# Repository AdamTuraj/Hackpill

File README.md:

# 

**The Hackboard may be overkill, but Hackpill is here to fill the smaller shoes!**

The Hackpill is a small but versatile board at a small cost.

Hackpill has the following features:

- 48MHz Cortex M0 Core with 32 Kb of Flash and 6 Kb of SRAM
- 32 GPIO pins
  - 1 SPI Interfaces
  - 1 I2C Interface
  - 1 CAN Interface
  - 1 USART Interface
  - 1 I2S Interface
  - 11 PWM Pins
  - 10 ADC's (Analog pins)
- An addressable LED
- USB C port for flashing and power

## Assembly

> [!CAUTION]
> The USBLC6 and diode may be orientated wrong. Ensure all components are properly orientated before ordering!

This board can be assembled through JLCPCB. The price for 5 assembled boards is around $35 USD without headers.

### Work with Arduino

> [!NOTE]
> You must have an STLink to continue. They can be bought standalone or with a Nucleo board.

A more detailed guide will be written up shortly. You may now use [STM32Duino](https://github.com/stm32duino/Arduino_Core_STM32) to make it work with Arduino.

## License

Hackclub is licensed under the MIT License. See the full license text in [LICENSE](LICENSE).

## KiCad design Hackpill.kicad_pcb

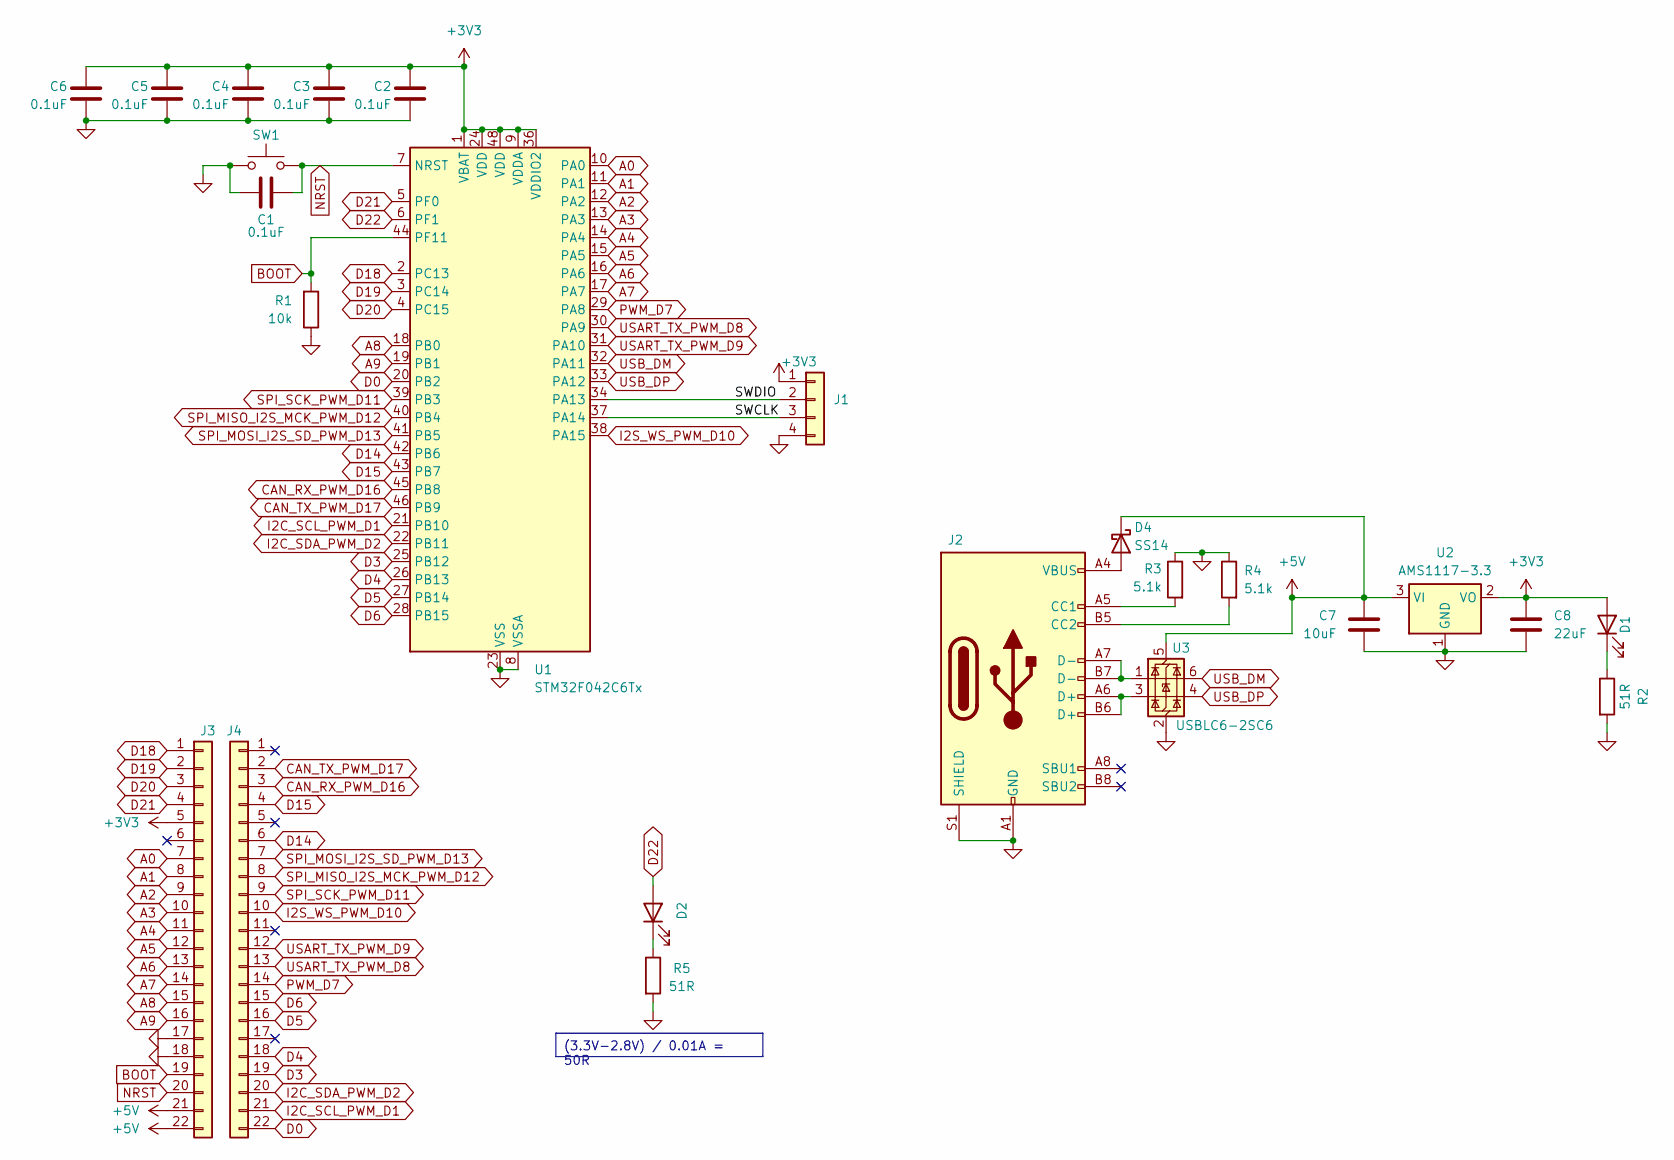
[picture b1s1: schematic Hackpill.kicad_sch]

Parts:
C1, C2, C3, C4, C5, C6: 0.1uF; C_0603_1608Metric
C7: 10uF; C_0603_1608Metric
C8: 22uF; C_0603_1608Metric
D1, D2: LED; LED_0805_2012Metric; LCSC C2297
D4: SS14; D_SMA
J1: Conn_01x04; PinHeader_1x04_P2.54mm_Vertical; LCSC C18905864
J2: USB_C_Receptacle_USB2.0_16P; USB_C_Receptacle_Shouhan_16P_TopMnt_Horizontal; LCSC C6332269
J3: Conn_01x22; PinSocket_1x22_P2.54mm_Vertical
J4: Conn_01x22; PinSocket_1x22_P2.54mm_Vertical; LCSC C18078140
R1: 10k; R_0603_1608Metric
R2, R5: 51R; R_0603_1608Metric
R3, R4: 5.1k; R_0603_1608Metric
SW1: SW_Push; SW_Push_1P1T_XKB_TS-1187A; LCSC C318884
U1: STM32F042C6Tx; LQFP-48_7x7mm_P0.5mm; LCSC C88447
U2: AMS1117-3.3; SOT-223-3_TabPin2; LCSC C6186
U3: USBLC6-2SC6; SOT-23-6; LCSC C2827654

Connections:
+3V3: C2.1, C3.1, C4.1, C5.1, C6.1, C8.1, D1.2 (A), J1.1, J3.5, U1.1 (VBAT), U1.9 (VDDA), U1.24 (VDD), U1.36 (VDDIO2), U1.48 (VDD), U2.2 (VO)
+5V: C7.1, D4.1 (K), J3.21, J3.22, U2.3 (VI), U3.5 (VBUS)
/SWCLK: J1.3, U1.37 (PA14)
/SWDIO: J1.2, U1.34 (PA13)
A0: J3.7, U1.10 (PA0)
A1: J3.8, U1.11 (PA1)
A2: J3.9, U1.12 (PA2)
A3: J3.10, U1.13 (PA3)
A4: J3.11, U1.14 (PA4)
A5: J3.12, U1.15 (PA5)
A6: J3.13, U1.16 (PA6)
A7: J3.14, U1.17 (PA7)
A8: J3.15, U1.18 (PB0)
A9: J3.16, U1.19 (PB1)
BOOT: J3.19, R1.2, U1.44 (PF11)
CAN_RX_PWM_D16: J4.3, U1.45 (PB8)
CAN_TX_PWM_D17: J4.2, U1.46 (PB9)
D0: J4.22, U1.20 (PB2)
D3: J4.19, U1.25 (PB12)
D4: J4.18, U1.26 (PB13)
D5: J4.16, U1.27 (PB14)
D6: J4.15, U1.28 (PB15)
D14: J4.6, U1.42 (PB6)
D15: J4.4, U1.43 (PB7)
D18: J3.1, U1.2 (PC13)
D19: J3.2, U1.3 (PC14)
D20: J3.3, U1.4 (PC15)
D21: J3.4, U1.5 (PF0)
D22: D2.2 (A), U1.6 (PF1)
GND: C1.1, C2.2, C3.2, C4.2, C5.2, C6.2, C7.2, C8.2, J1.4, J2.A1 (GND), J2.A12 (GND), J2.B1 (GND), J2.B12 (GND), J2.S1 (SHIELD), J3.17, J3.18, R1.1, R2.2, R3.1, R4.1, R5.2, SW1.1, U1.8 (VSSA), U1.23 (VSS), U1.35 (VSS), U1.47 (VSS), U2.1 (GND), U3.2 (GND)
I2C_SCL_PWM_D1: J4.21, U1.21 (PB10)
I2C_SDA_PWM_D2: J4.20, U1.22 (PB11)
I2S_WS_PWM_D10: J4.10, U1.38 (PA15)
NRST: C1.2, J3.20, SW1.2, U1.7 (NRST)
unnamed: D1.1 (K), R2.1
unnamed: D2.1 (K), R5.1
unnamed: D4.2 (A), J2.A4 (VBUS), J2.A9 (VBUS), J2.B4 (VBUS), J2.B9 (VBUS)
unnamed: J2.A5 (CC1), R3.2
unnamed: J2.B5 (CC2), R4.2
unnamed: J2.A6 (D+), J2.B6 (D+), U3.3 (I/O2)
unnamed: J2.A7 (D-), J2.B7 (D-), U3.1 (I/O1)
PWM_D7: J4.14, U1.29 (PA8)
SPI_MISO_I2S_MCK_PWM_D12: J4.8, U1.40 (PB4)
SPI_MOSI_I2S_SD_PWM_D13: J4.7, U1.41 (PB5)
SPI_SCK_PWM_D11: J4.9, U1.39 (PB3)
USART_TX_PWM_D8: J4.13, U1.30 (PA9)
USART_TX_PWM_D9: J4.12, U1.31 (PA10)
USB_DM: U1.32 (PA11), U3.6 (I/O1)
USB_DP: U1.33 (PA12), U3.4 (I/O2)

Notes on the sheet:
(3.3V-2.8V) / 0.01A = 50R

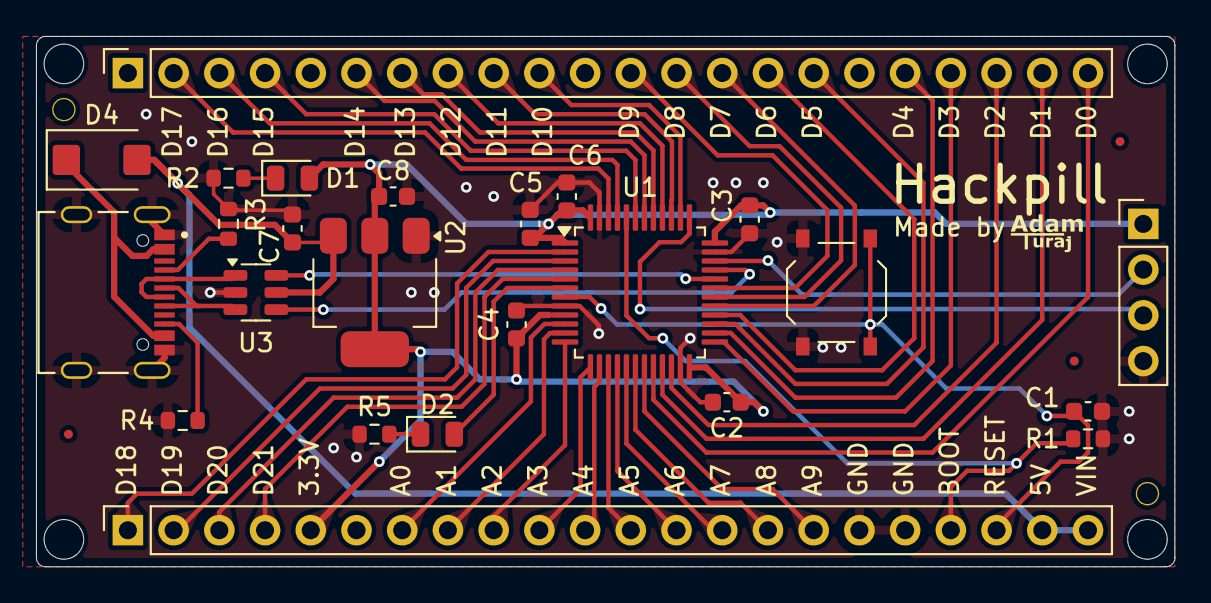
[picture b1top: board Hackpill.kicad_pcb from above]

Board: 2 copper layers, 63.2 x 29.5 mm, 24 parts (0 on the bottom side), 49 nets.

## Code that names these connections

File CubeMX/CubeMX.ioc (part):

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Mcu.Name=STM32F042C(4-6)Tx
Mcu.Package=LQFP48
Mcu.UserName=STM32F042C6Tx
PA0.GPIOParameters=GPIO_Label
PA0.GPIO_Label=A9
PA0.Mode=IN0
PA0.Signal=ADC_IN0
PA1.GPIOParameters=GPIO_Label
PA1.GPIO_Label=A8
PA1.Mode=IN1
PA1.Signal=ADC_IN1
PA10.GPIOParameters=GPIO_Label
PA10.GPIO_Label=USART_RX_PWM_D9
PA10.Signal=S_TIM1_CH3
PA11.GPIOParameters=GPIO_Label
PA11.GPIO_Label=USB_DM
PA11.Mode=Device
PA11.Signal=USB_DM
PA12.GPIOParameters=GPIO_Label
PA12.GPIO_Label=USB_DP
PA12.Mode=Device
PA12.Signal=USB_DP
PA13.Mode=Serial_Wire
PA13.Signal=SYS_SWDIO
PA14.Mode=Serial_Wire
PA14.Signal=SYS_SWCLK
PA15.GPIOParameters=GPIO_Label
PA15.GPIO_Label=I2S_WS_PWM_D10
PA15.Signal=S_TIM2_CH1_ETR
PA2.GPIOParameters=GPIO_Label
PA2.GPIO_Label=A7
PA2.Mode=IN2
PA2.Signal=ADC_IN2
PA3.GPIOParameters=GPIO_Label
PA3.GPIO_Label=A6
PA3.Mode=IN3
PA3.Signal=ADC_IN3
PA4.GPIOParameters=GPIO_Label
PA4.GPIO_Label=A5
PA4.Mode=IN4
PA4.Signal=ADC_IN4
PA5.GPIOParameters=GPIO_Label
PA5.GPIO_Label=A4
PA5.Mode=IN5
PA5.Signal=ADC_IN5
PA6.GPIOParameters=GPIO_Label
PA6.GPIO_Label=A3
PA6.Mode=IN6
PA6.Signal=ADC_IN6
PA7.GPIOParameters=GPIO_Label
PA7.GPIO_Label=A2
PA7.Mode=IN7
PA7.Signal=ADC_IN7
PA8.GPIOParameters=GPIO_Label
PA8.GPIO_Label=PWM_D7
PA8.Signal=S_TIM1_CH1
PA9.GPIOParameters=GPIO_Label
PA9.GPIO_Label=USART_TX_PWM_D8
PA9.Signal=S_TIM1_CH2
PB0.GPIOParameters=GPIO_Label
PB0.GPIO_Label=A1
PB0.Mode=IN8
PB0.Signal=ADC_IN8
PB1.GPIOParameters=GPIO_Label
PB1.GPIO_Label=A0
PB1.Mode=IN9
PB1.Signal=ADC_IN9
PB10.GPIOParameters=GPIO_Label
PB10.GPIO_Label=I2C_SCL_PWM_D1
PB10.Signal=S_TIM2_CH3
PB11.GPIOParameters=GPIO_Label
PB11.GPIO_Label=I2C_SDA_PWM_D2
PB11.Signal=S_TIM2_CH4
PB12.GPIOParameters=GPIO_Label
PB12.GPIO_Label=D3
PB12.Signal=GPIO_Input
PB13.GPIOParameters=GPIO_Label
PB13.GPIO_Label=D4
PB13.Signal=GPIO_Input
PB14.GPIOParameters=GPIO_Label
PB14.GPIO_Label=D5
PB14.Signal=GPIO_Input
PB15.GPIOParameters=GPIO_Label
PB15.GPIO_Label=D6
PB15.Signal=GPIO_Input
PB2.GPIOParameters=GPIO_Label
PB2.GPIO_Label=D0
PB2.Signal=GPIO_Input
PB3.GPIOParameters=GPIO_Label
PB3.GPIO_Label=SPI_SCK_PWM_D11
PB3.Signal=S_TIM2_CH2
PB4.GPIOParameters=GPIO_Label
PB4.GPIO_Label=SPI_MISO_I2S_MCK_PWM_D12
PB4.Signal=S_TIM3_CH1
PB5.GPIOParameters=GPIO_Label
PB5.GPIO_Label=SPI_MOSI_I2S_SD_PWM_D13
PB5.Signal=S_TIM3_CH2
PB6.GPIOParameters=GPIO_Label
PB6.GPIO_Label=D14
PB6.Signal=GPIO_Input
PB7.GPIOParameters=GPIO_Label
PB7.GPIO_Label=D15
PB7.Signal=GPIO_Input
PB8.GPIOParameters=GPIO_Label
PB8.GPIO_Label=CAN_RX_PWM_D16
PB8.Signal=S_TIM16_CH1
PB9.GPIOParameters=GPIO_Label
PB9.GPIO_Label=CAN_TX_PWM_D17
PB9.Signal=S_TIM17_CH1
PC13.GPIOParameters=GPIO_Label
PC13.GPIO_Label=D18
PC13.Signal=GPIO_Input
PC14OSC32_IN.GPIOParameters=GPIO_Label
PC14OSC32_IN.GPIO_Label=D19
PC14OSC32_IN.Signal=GPIO_Input
PC15OSC32_OUT.GPIOParameters=GPIO_Label
PC15OSC32_OUT.GPIO_Label=D20
PC15OSC32_OUT.Signal=GPIO_Input
PF0-OSC_IN.GPIOParameters=GPIO_Label
PF0-OSC_IN.GPIO_Label=D21
PF0-OSC_IN.Signal=GPIO_Input
PF1-OSC_OUT.GPIOParameters=GPIO_Label
PF1-OSC_OUT.GPIO_Label=D22
PF1-OSC_OUT.Signal=GPIO_Input
PF11.GPIOParameters=GPIO_Label
PF11.GPIO_Label=BOOT
PF11.Signal=GPIO_Input
RCC.SYSCLKFreq_VALUE=48000000
RCC.SYSCLKSource=RCC_SYSCLKSOURCE_HSI48
board=custom

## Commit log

2024-08-15 First commit!
2024-08-15 Finish schematic, assign components and footprints
2024-08-15 Finish component selection and footprint assignment
2024-08-15 Start tracing board
2024-08-15 Finish PCB
2024-08-16 Adjust trace width, adjust pinout, make changes to schematic
2024-08-16 Complete fixes for PCB
2024-08-16 Add diode to USB, rename files, add prod files
2024-08-26 Change clearence, update footprint, add README, add schematic, remove config file
